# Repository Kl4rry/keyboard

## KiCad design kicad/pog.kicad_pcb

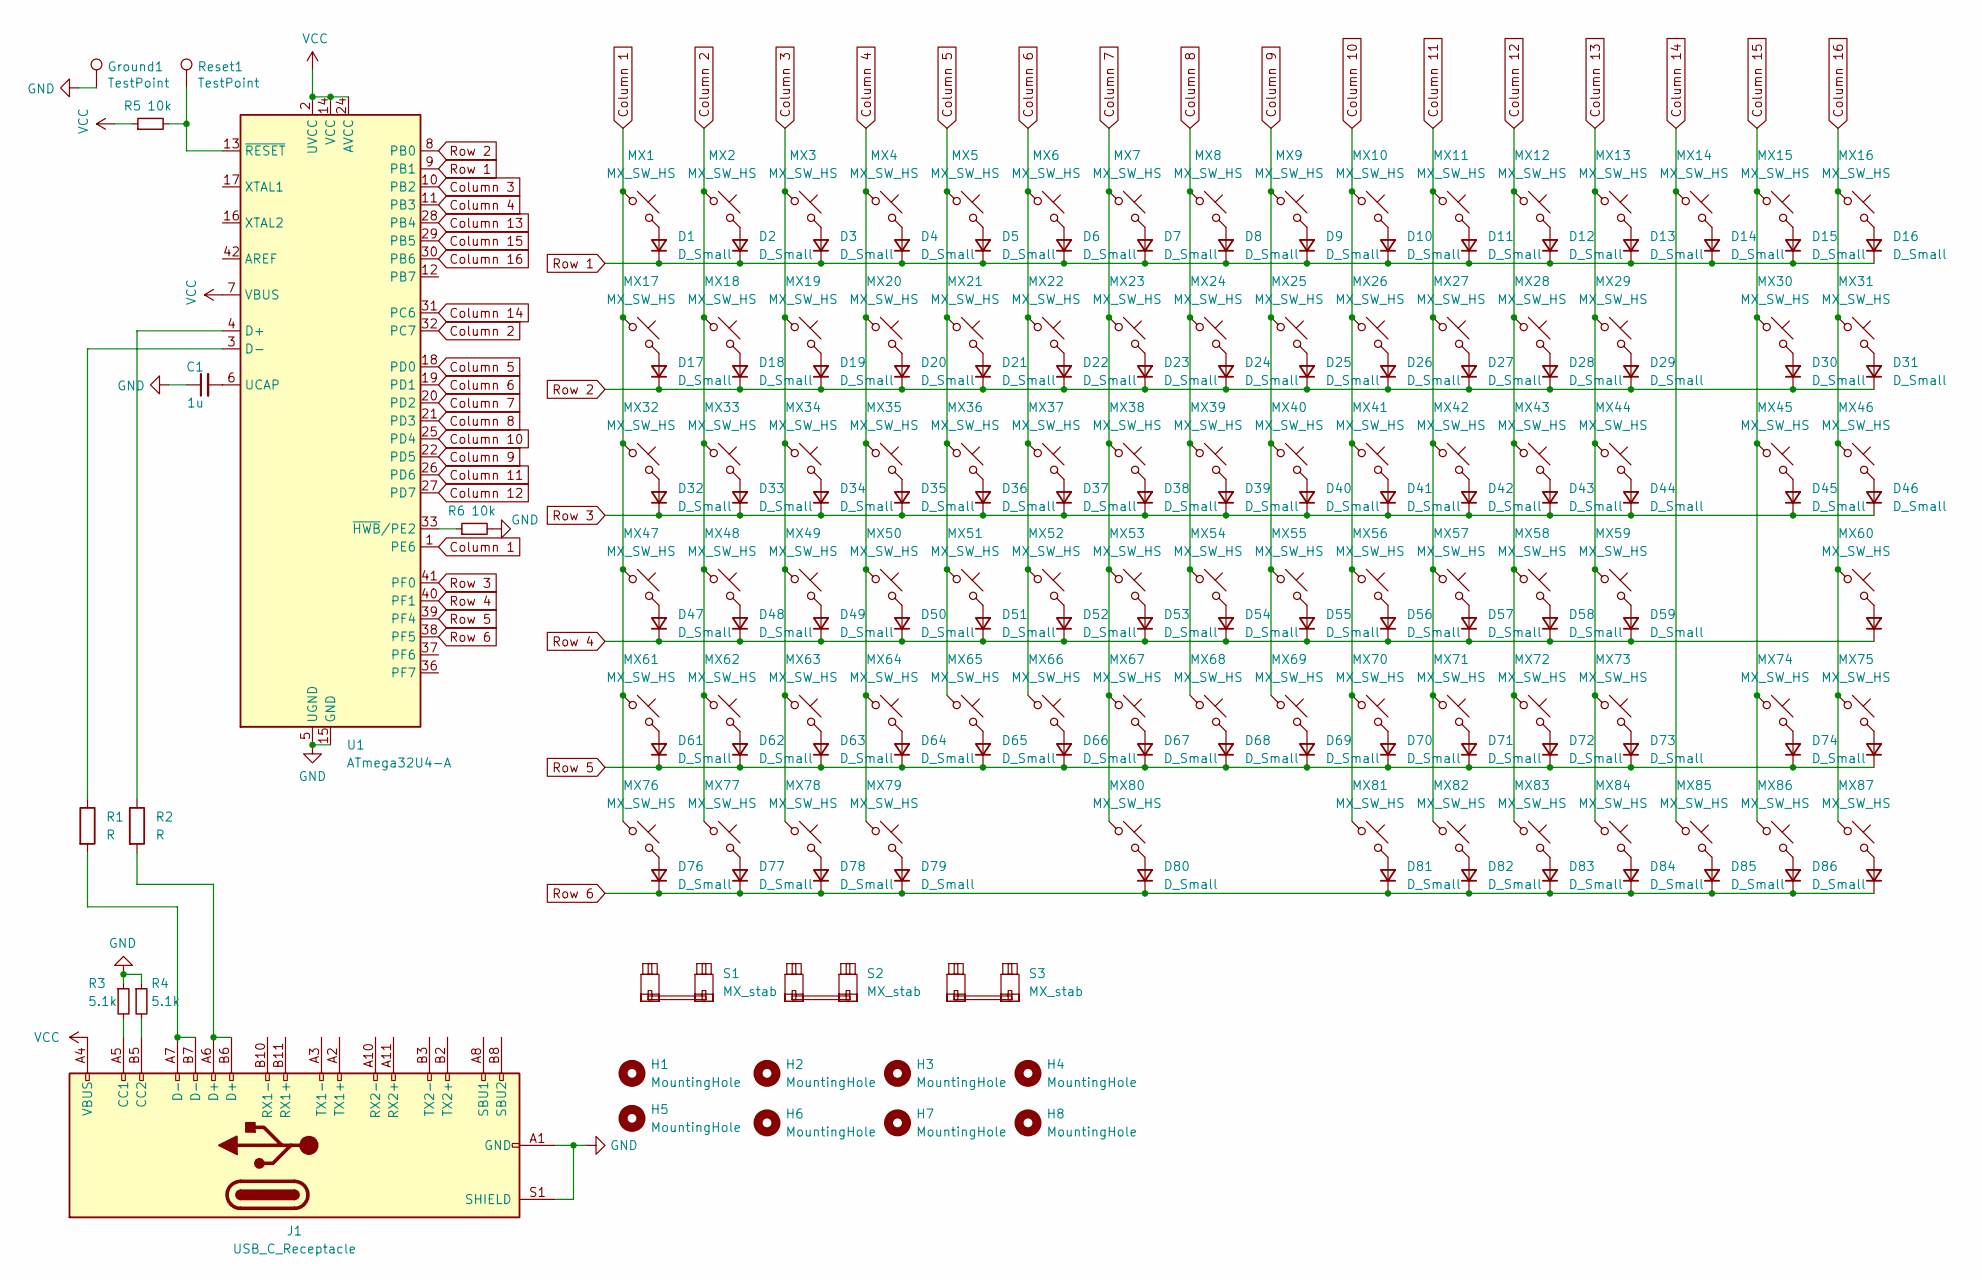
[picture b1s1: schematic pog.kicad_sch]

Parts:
C1: 1u; C_1206_3216Metric
D1, D2, D3, D4, D5, D6, D7, D8, D9, D10, D11, D12, D13, D14, D15, D16, D17, D18, D19, D20, D21, D22, D23, D24, D25, D26, D27, D28, D29, D30, D31, D32, D33, D34, D35, D36, D37, D38, D39, D40, D41, D42, D43, D44, D45, D46, D47, D48, D49, D50, D51, D52, D53, D54, D55, D56, D57, D58, D59, D60, D61, D62, D63, D64, D65, D66, D67, D68, D69, D70, D71, D72, D73, D74, D75, D76, D77, D78, D79, D80, D81, D82, D83, D84, D85, D86, D87: D_Small; D_SOD-123
Ground1: TestPoint; TestPoint_THTPad_2.0x2.0mm_Drill1.0mm
H1, H2, H3, H4, H5, H6, H7, H8: MountingHole; MountingHole_2.1mm
J1: USB_C_Receptacle; USB_C_Receptacle_HRO_TYPE-C-31-M-12
MX1, MX2, MX3, MX4, MX5, MX6, MX7, MX8, MX9, MX10, MX11, MX12, MX13, MX14, MX15, MX16, MX17, MX18, MX19, MX20, MX21, MX22, MX23, MX24, MX25, MX26, MX27, MX28, MX29, MX30, MX31, MX33, MX34, MX35, MX36, MX37, MX38, MX39, MX40, MX41, MX42, MX43, MX44, MX45, MX46, MX48, MX49, MX50, MX51, MX52, MX53, MX54, MX55, MX56, MX57, MX58, MX59, MX60, MX62, MX63, MX64, MX65, MX66, MX67, MX68, MX69, MX70, MX71, MX72, MX74, MX75, MX77, MX79, MX80, MX81, MX82, MX83, MX84, MX85, MX86, MX87: MX_SW_HS; SW_MX_HS_1u
MX32: MX_SW_HS; SW_MX_HS_1.5u
MX47, MX73: MX_SW_HS; SW_MX_HS_1.75u
MX61, MX76, MX78: MX_SW_HS; SW_MX_HS_1.25u
R1, R2: R; R_1206_3216Metric
R3, R4: 5.1k; R_1206_3216Metric
R5, R6: 10k; R_1206_3216Metric
Reset1: TestPoint; TestPoint_THTPad_2.0x2.0mm_Drill1.0mm
S1: MX_stab; STAB_MX_2u
S2: MX_stab; STAB_MX_ISO
S3: MX_stab; STAB_MX_4.5u
U1: ATmega32U4-A; TQFP-44_10x10mm_P0.8mm

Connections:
Column 1: MX1.1, MX17.1, MX32.1, MX47.1, MX61.1, MX76.1, U1.1 (PE6)
Column 2: MX2.1, MX18.1, MX33.1, MX48.1, MX62.1, MX77.1, U1.32 (PC7)
Column 3: MX3.1, MX19.1, MX34.1, MX49.1, MX63.1, MX78.1, U1.10 (PB2)
Column 4: MX4.1, MX20.1, MX35.1, MX50.1, MX64.1, MX79.1, U1.11 (PB3)
Column 5: MX5.1, MX21.1, MX36.1, MX51.1, MX65.1, U1.18 (PD0)
Column 6: MX6.1, MX22.1, MX37.1, MX52.1, MX66.1, U1.19 (PD1)
Column 7: MX7.1, MX23.1, MX38.1, MX53.1, MX67.1, MX80.1, U1.20 (PD2)
Column 8: MX8.1, MX24.1, MX39.1, MX54.1, MX68.1, U1.21 (PD3)
Column 9: MX9.1, MX25.1, MX40.1, MX55.1, MX69.1, U1.22 (PD5)
Column 10: MX10.1, MX26.1, MX41.1, MX56.1, MX70.1, MX81.1, U1.25 (PD4)
Column 11: MX11.1, MX27.1, MX42.1, MX57.1, MX71.1, MX82.1, U1.26 (PD6)
Column 12: MX12.1, MX28.1, MX43.1, MX58.1, MX72.1, MX83.1, U1.27 (PD7)
Column 13: MX13.1, MX29.1, MX44.1, MX59.1, MX73.1, MX84.1, U1.28 (PB4)
Column 14: MX14.1, MX85.1, U1.31 (PC6)
Column 15: MX15.1, MX30.1, MX45.1, MX74.1, MX86.1, U1.29 (PB5)
Column 16: MX16.1, MX31.1, MX46.1, MX60.1, MX75.1, MX87.1, U1.30 (PB6)
GND: C1.1, Ground1.1, J1.A1 (GND), J1.A12 (GND), J1.B1 (GND), J1.B12 (GND), J1.S1 (SHIELD), R3.1, R4.1, R6.2, U1.5 (UGND), U1.15 (GND), U1.23 (GND), U1.35 (GND), U1.43 (GND)
unnamed: D1.2 (A), MX1.2
unnamed: D2.2 (A), MX2.2
unnamed: D3.2 (A), MX3.2
unnamed: D4.2 (A), MX4.2
unnamed: D5.2 (A), MX5.2
unnamed: D6.2 (A), MX6.2
unnamed: D7.2 (A), MX7.2
unnamed: D8.2 (A), MX8.2
unnamed: D9.2 (A), MX9.2
unnamed: D10.2 (A), MX10.2
unnamed: D11.2 (A), MX11.2
unnamed: D12.2 (A), MX12.2
unnamed: D13.2 (A), MX13.2
unnamed: D14.2 (A), MX14.2
unnamed: D15.2 (A), MX15.2
unnamed: D16.2 (A), MX16.2
unnamed: D17.2 (A), MX17.2
unnamed: D18.2 (A), MX18.2
unnamed: D19.2 (A), MX19.2
unnamed: D20.2 (A), MX20.2
unnamed: D21.2 (A), MX21.2
unnamed: D22.2 (A), MX22.2
unnamed: D23.2 (A), MX23.2
unnamed: D24.2 (A), MX24.2
unnamed: D25.2 (A), MX25.2
unnamed: D26.2 (A), MX26.2
unnamed: D27.2 (A), MX27.2
unnamed: D28.2 (A), MX28.2
unnamed: D29.2 (A), MX29.2
unnamed: D30.2 (A), MX30.2
unnamed: D31.2 (A), MX31.2
unnamed: D32.2 (A), MX32.2
unnamed: D33.2 (A), MX33.2
unnamed: D34.2 (A), MX34.2
unnamed: D35.2 (A), MX35.2
unnamed: D36.2 (A), MX36.2
unnamed: D37.2 (A), MX37.2
unnamed: D38.2 (A), MX38.2
unnamed: D39.2 (A), MX39.2
unnamed: D40.2 (A), MX40.2
unnamed: D41.2 (A), MX41.2
unnamed: D42.2 (A), MX42.2
unnamed: D43.2 (A), MX43.2
unnamed: D44.2 (A), MX44.2
unnamed: D45.2 (A), MX45.2
unnamed: D46.2 (A), MX46.2
unnamed: D47.2 (A), MX47.2
unnamed: D48.2 (A), MX48.2
unnamed: D49.2 (A), MX49.2
unnamed: D50.2 (A), MX50.2
unnamed: D51.2 (A), MX51.2
unnamed: D52.2 (A), MX52.2
unnamed: D53.2 (A), MX53.2
unnamed: D54.2 (A), MX54.2
unnamed: D55.2 (A), MX55.2
unnamed: D56.2 (A), MX56.2
unnamed: D57.2 (A), MX57.2
unnamed: D58.2 (A), MX58.2
unnamed: D59.2 (A), MX59.2
unnamed: D60.2 (A), MX60.2
unnamed: D61.2 (A), MX61.2
unnamed: D62.2 (A), MX62.2
unnamed: D63.2 (A), MX63.2
unnamed: D64.2 (A), MX64.2
unnamed: D65.2 (A), MX65.2
unnamed: D66.2 (A), MX66.2
unnamed: D67.2 (A), MX67.2
unnamed: D68.2 (A), MX68.2
unnamed: D69.2 (A), MX69.2
unnamed: D70.2 (A), MX70.2
unnamed: D71.2 (A), MX71.2
unnamed: D72.2 (A), MX72.2
unnamed: D73.2 (A), MX73.2
unnamed: D74.2 (A), MX74.2
unnamed: D75.2 (A), MX75.2
unnamed: D76.2 (A), MX76.2
unnamed: D77.2 (A), MX77.2
unnamed: D78.2 (A), MX78.2
unnamed: D79.2 (A), MX79.2
unnamed: D80.2 (A), MX80.2
unnamed: D81.2 (A), MX81.2
unnamed: D82.2 (A), MX82.2
unnamed: D83.2 (A), MX83.2
unnamed: D84.2 (A), MX84.2
unnamed: D85.2 (A), MX85.2
unnamed: D86.2 (A), MX86.2
unnamed: D87.2 (A), MX87.2
unnamed: J1.A5 (CC1), R3.2
unnamed: J1.B5 (CC2), R4.2
unnamed: J1.A6 (D+), J1.B6 (D+), R2.2
unnamed: J1.A7 (D-), J1.B7 (D-), R1.2
unnamed: R2.1, U1.4 (D+)
unnamed: R1.1, U1.3 (D-)
unnamed: C1.2, U1.6 (UCAP)
unnamed: R6.1, U1.33 (~HWB/PE2)
unnamed: R5.2, Reset1.1, U1.13 (~RESET)
Row 1: D1.1 (K), D2.1 (K), D3.1 (K), D4.1 (K), D5.1 (K), D6.1 (K), D7.1 (K), D8.1 (K), D9.1 (K), D10.1 (K), D11.1 (K), D12.1 (K), D13.1 (K), D14.1 (K), D15.1 (K), D16.1 (K), U1.9 (PB1)
Row 2: D17.1 (K), D18.1 (K), D19.1 (K), D20.1 (K), D21.1 (K), D22.1 (K), D23.1 (K), D24.1 (K), D25.1 (K), D26.1 (K), D27.1 (K), D28.1 (K), D29.1 (K), D30.1 (K), D31.1 (K), U1.8 (PB0)
Row 3: D32.1 (K), D33.1 (K), D34.1 (K), D35.1 (K), D36.1 (K), D37.1 (K), D38.1 (K), D39.1 (K), D40.1 (K), D41.1 (K), D42.1 (K), D43.1 (K), D44.1 (K), D45.1 (K), D46.1 (K), U1.41 (PF0)
Row 4: D47.1 (K), D48.1 (K), D49.1 (K), D50.1 (K), D51.1 (K), D52.1 (K), D53.1 (K), D54.1 (K), D55.1 (K), D56.1 (K), D57.1 (K), D58.1 (K), D59.1 (K), D60.1 (K), U1.40 (PF1)
Row 5: D61.1 (K), D62.1 (K), D63.1 (K), D64.1 (K), D65.1 (K), D66.1 (K), D67.1 (K), D68.1 (K), D69.1 (K), D70.1 (K), D71.1 (K), D72.1 (K), D73.1 (K), D74.1 (K), D75.1 (K), U1.39 (PF4)
Row 6: D76.1 (K), D77.1 (K), D78.1 (K), D79.1 (K), D80.1 (K), D81.1 (K), D82.1 (K), D83.1 (K), D84.1 (K), D85.1 (K), D86.1 (K), D87.1 (K), U1.38 (PF5)
VCC: J1.A4 (VBUS), J1.A9 (VBUS), J1.B4 (VBUS), J1.B9 (VBUS), R5.1, U1.2 (UVCC), U1.7 (VBUS), U1.14 (VCC), U1.24 (AVCC), U1.34 (VCC), U1.44 (AVCC)

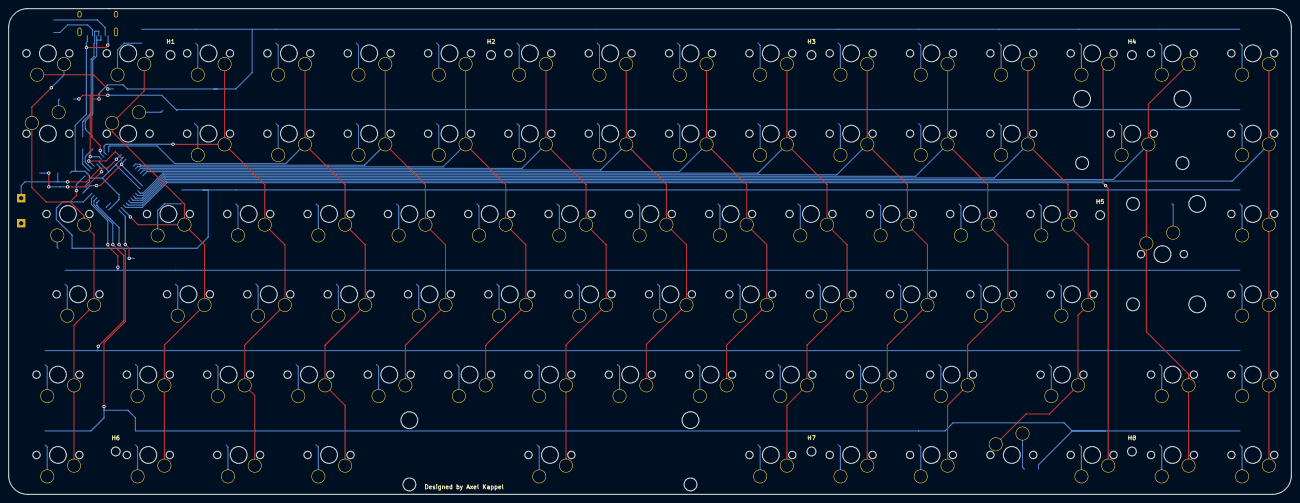
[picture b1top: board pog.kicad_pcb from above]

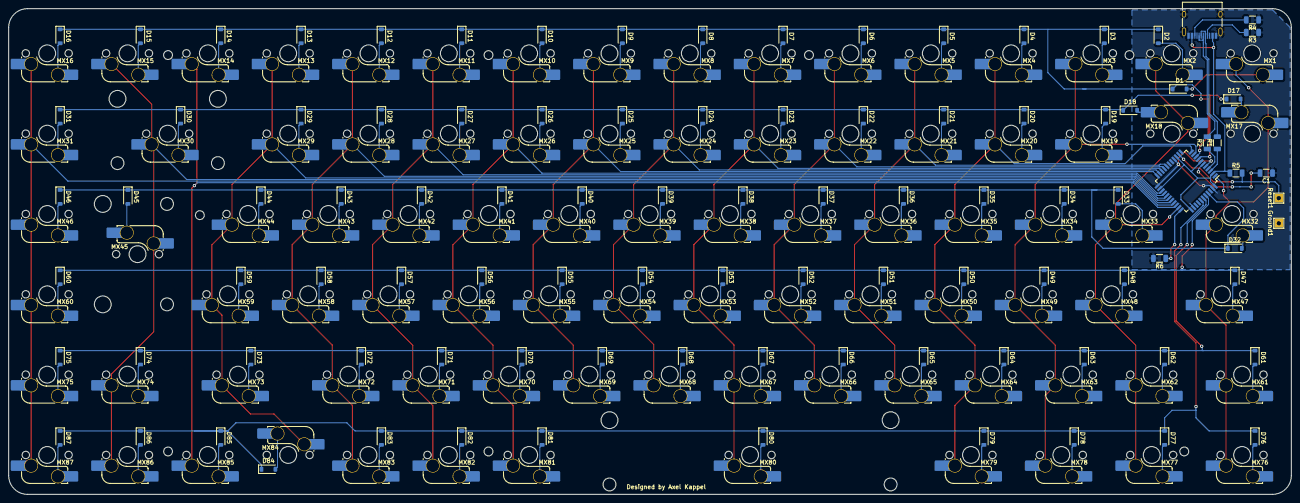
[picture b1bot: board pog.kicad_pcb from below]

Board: 2 copper layers, 304.2 x 115.2 mm, 196 parts (185 on the bottom side), 120 nets.

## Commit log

2023-08-29 more traces and git ignore update
2023-09-01 schematic done
2023-09-02 complete basic pcb design
2023-09-03 pre switch flip
2023-09-03 pcb done except for ground
2023-09-03 add grounding plane
2023-09-10 finished keyboard
2023-09-10 switch to pcb mount stabilizers
